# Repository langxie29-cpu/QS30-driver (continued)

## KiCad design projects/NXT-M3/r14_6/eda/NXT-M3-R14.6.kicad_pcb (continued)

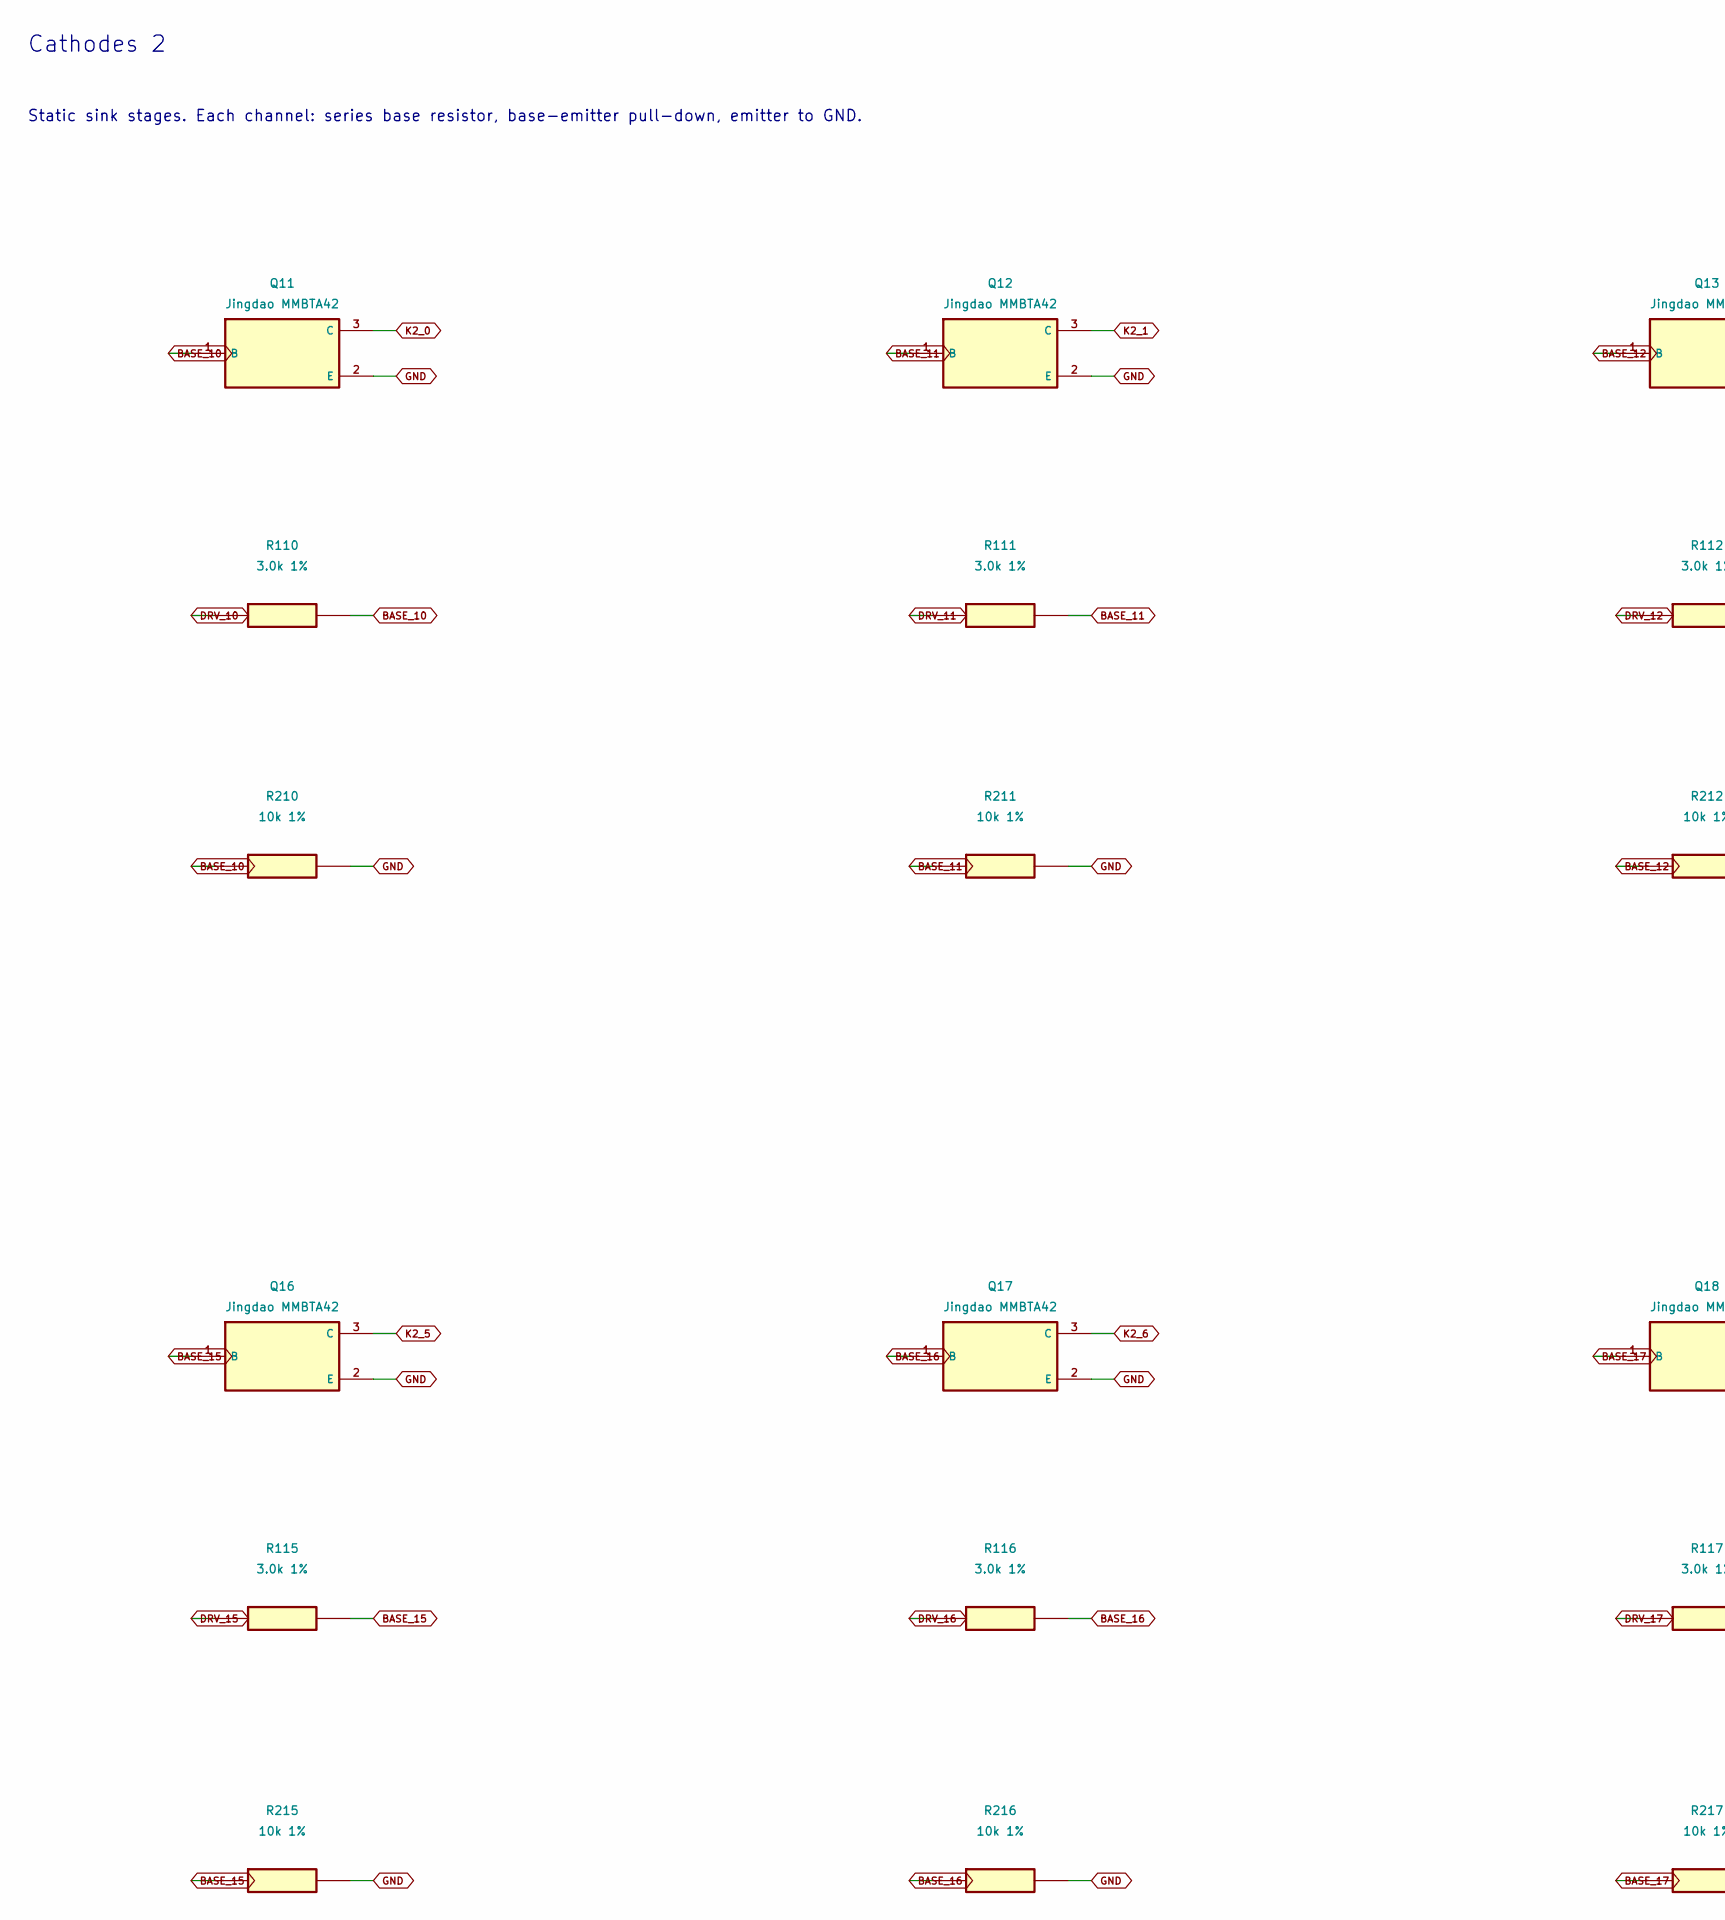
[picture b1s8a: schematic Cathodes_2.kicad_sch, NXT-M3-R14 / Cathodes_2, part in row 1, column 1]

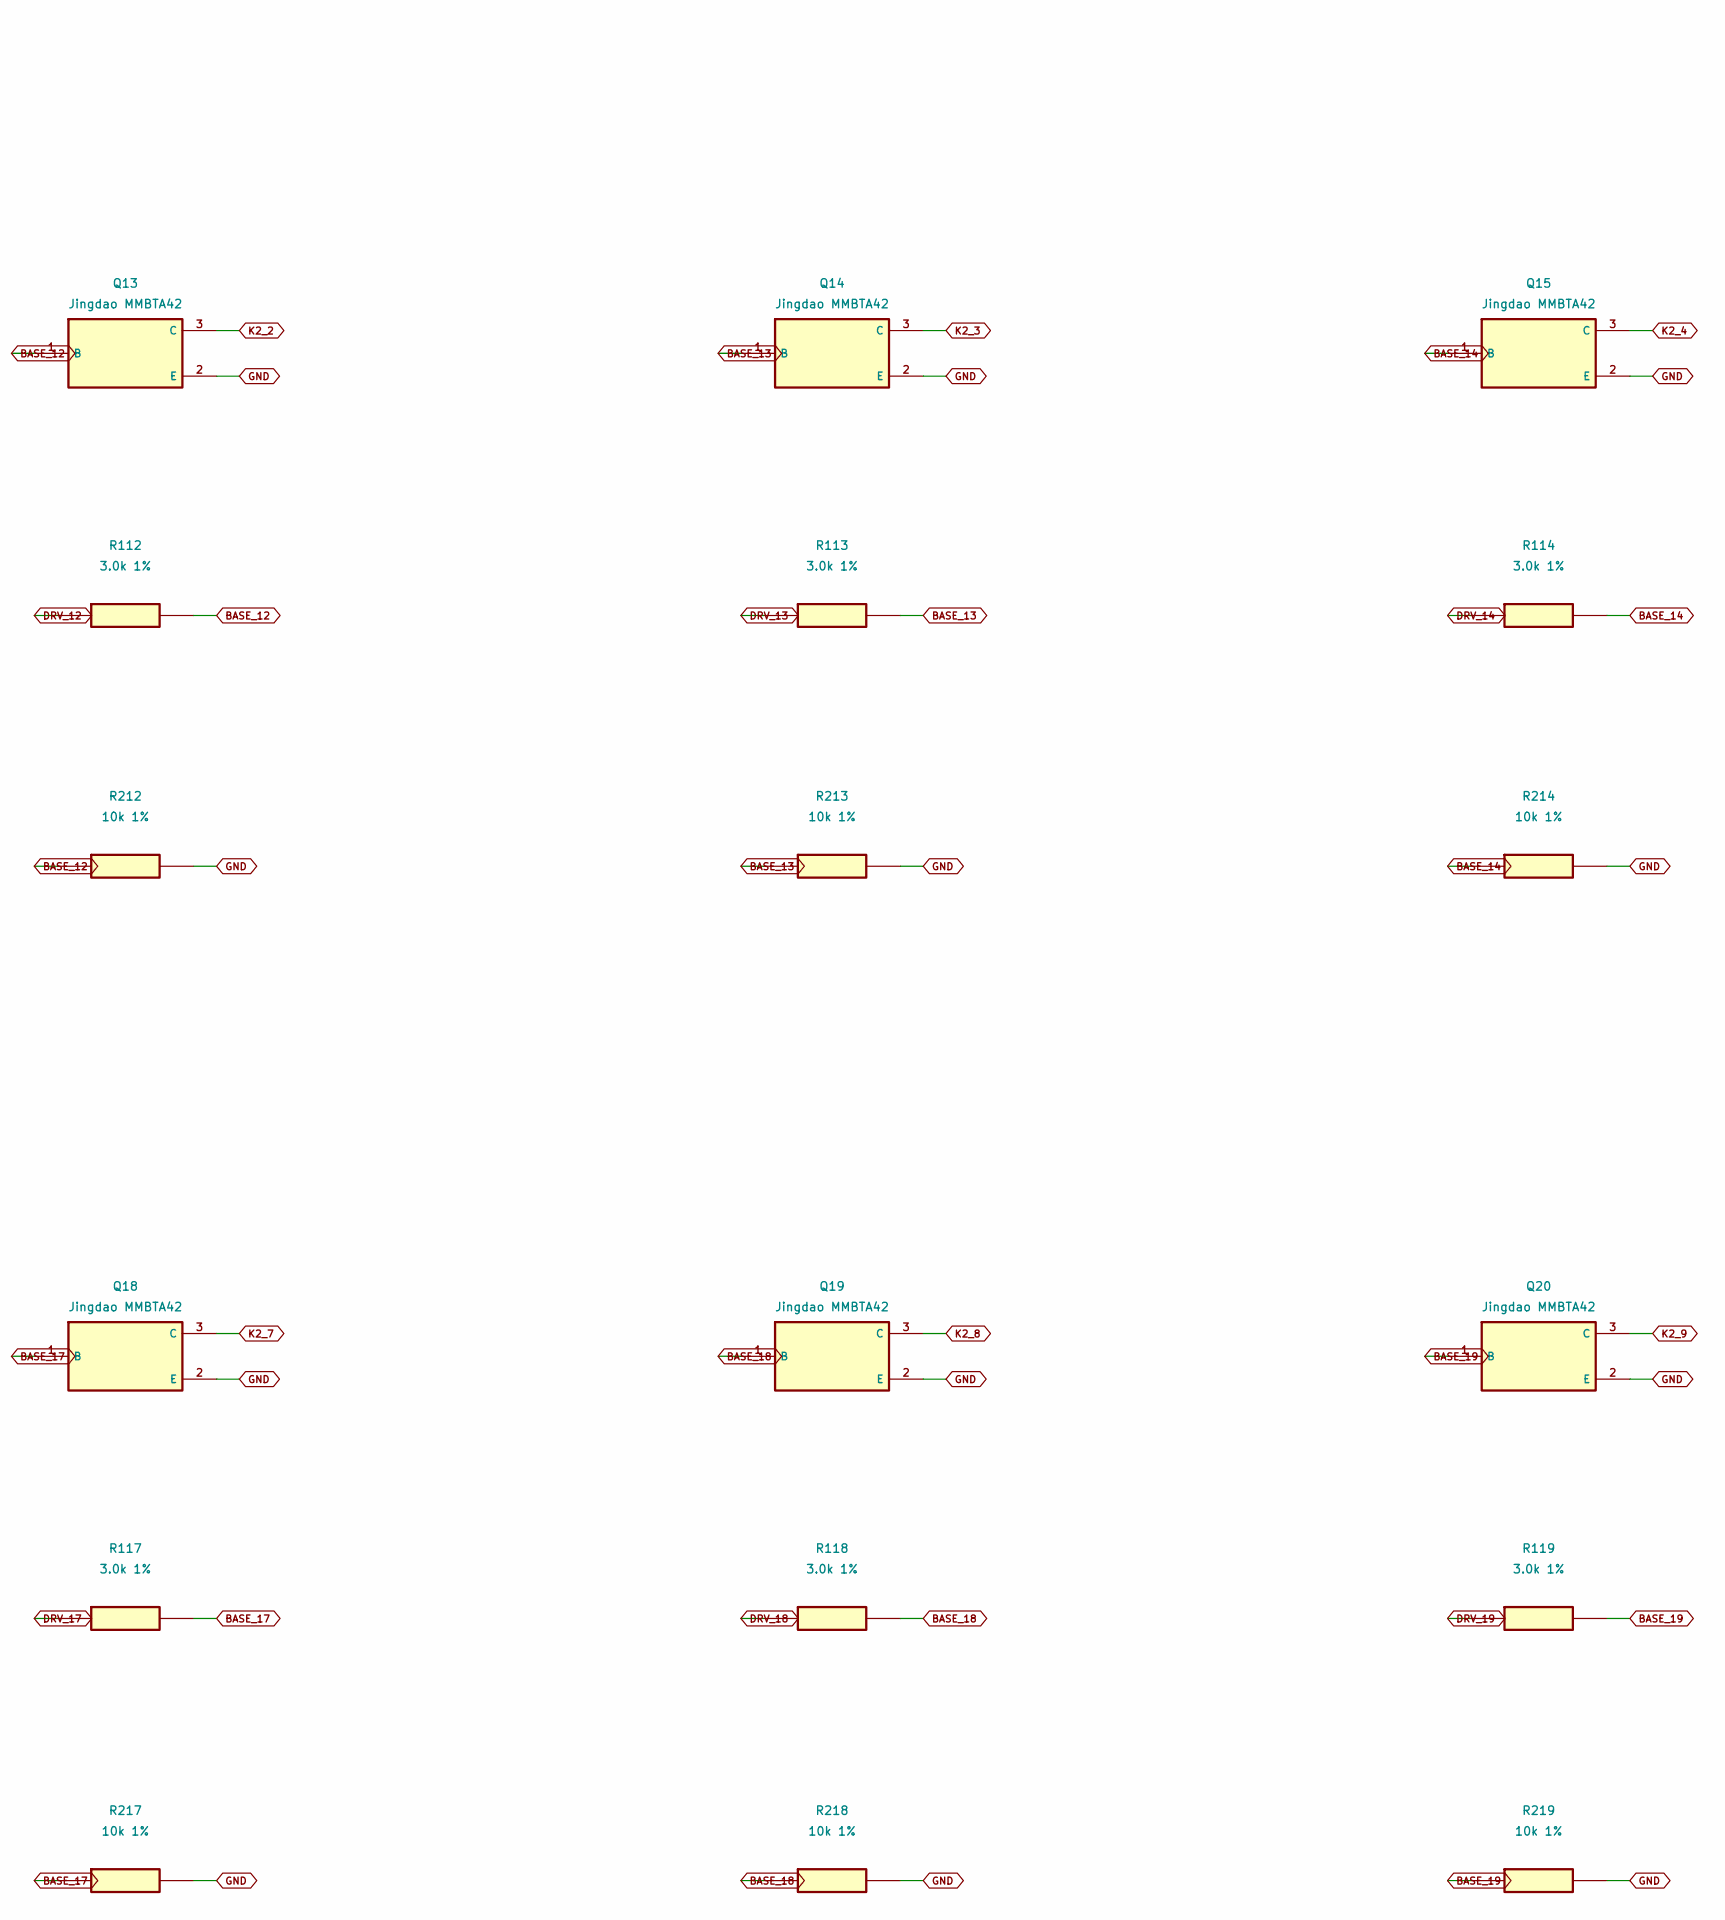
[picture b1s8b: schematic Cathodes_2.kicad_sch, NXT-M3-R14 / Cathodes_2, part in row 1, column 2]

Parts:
Q11, Q12, Q13, Q14, Q15, Q16, Q17, Q18, Q19, Q20: Jingdao MMBTA42; Jingdao_MMBTA42_nominal; MPN MMBTA42 / C4749118
R110, R111, R112, R113, R114, R115, R116, R117, R118, R119: 3.0k 1%; R_0603_1608Metric; MPN RC0603FR-073KL
R210, R211, R212, R213, R214, R215, R216, R217, R218, R219: 10k 1%; R_0603_1608Metric; MPN RC0603FR-0710KL

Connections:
BASE_10: Q11.1 (B), R110.2, R210.1
BASE_11: Q12.1 (B), R111.2, R211.1
BASE_12: Q13.1 (B), R112.2, R212.1
BASE_13: Q14.1 (B), R113.2, R213.1
BASE_14: Q15.1 (B), R114.2, R214.1
BASE_15: Q16.1 (B), R115.2, R215.1
BASE_16: Q17.1 (B), R116.2, R216.1
BASE_17: Q18.1 (B), R117.2, R217.1
BASE_18: Q19.1 (B), R118.2, R218.1
BASE_19: Q20.1 (B), R119.2, R219.1
DRV_10: R110.1; also elsewhere on the board
DRV_11: R111.1; also elsewhere on the board
DRV_12: R112.1; also elsewhere on the board
DRV_13: R113.1; also elsewhere on the board
DRV_14: R114.1; also elsewhere on the board
DRV_15: R115.1; also elsewhere on the board
DRV_16: R116.1; also elsewhere on the board
DRV_17: R117.1; also elsewhere on the board
DRV_18: R118.1; also elsewhere on the board
DRV_19: R119.1; also elsewhere on the board
GND: Q11.2 (E), Q12.2 (E), Q13.2 (E), Q14.2 (E), Q15.2 (E), Q16.2 (E), Q17.2 (E), Q18.2 (E), Q19.2 (E), Q20.2 (E), R210.2, R211.2, R212.2, R213.2, R214.2, R215.2, R216.2, R217.2, R218.2, R219.2; also elsewhere on the board
K2_0: Q11.3 (C); also elsewhere on the board
K2_1: Q12.3 (C); also elsewhere on the board
K2_2: Q13.3 (C); also elsewhere on the board
K2_3: Q14.3 (C); also elsewhere on the board
K2_4: Q15.3 (C); also elsewhere on the board
K2_5: Q16.3 (C); also elsewhere on the board
K2_6: Q17.3 (C); also elsewhere on the board
K2_7: Q18.3 (C); also elsewhere on the board
K2_8: Q19.3 (C); also elsewhere on the board
K2_9: Q20.3 (C); also elsewhere on the board

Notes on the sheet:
Cathodes 2
Static sink stages. Each channel: series base resistor, base-emitter pull-down, emitter to GND.

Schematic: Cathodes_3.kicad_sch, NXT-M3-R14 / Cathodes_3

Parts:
Q21, Q22, Q23, Q24, Q25, Q26, Q27, Q28, Q29, Q30: Jingdao MMBTA42; Jingdao_MMBTA42_nominal; MPN MMBTA42 / C4749118
R120, R121, R122, R123, R124, R125, R126, R127, R128, R129: 3.0k 1%; R_0603_1608Metric; MPN RC0603FR-073KL
R220, R221, R222, R223, R224, R225, R226, R227, R228, R229: 10k 1%; R_0603_1608Metric; MPN RC0603FR-0710KL

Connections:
BASE_20: Q21.1 (B), R120.2, R220.1
BASE_21: Q22.1 (B), R121.2, R221.1
BASE_22: Q23.1 (B), R122.2, R222.1
BASE_23: Q24.1 (B), R123.2, R223.1
BASE_24: Q25.1 (B), R124.2, R224.1
BASE_25: Q26.1 (B), R125.2, R225.1
BASE_26: Q27.1 (B), R126.2, R226.1
BASE_27: Q28.1 (B), R127.2, R227.1
BASE_28: Q29.1 (B), R128.2, R228.1
BASE_29: Q30.1 (B), R129.2, R229.1
DRV_20: R120.1; also elsewhere on the board
DRV_21: R121.1; also elsewhere on the board
DRV_22: R122.1; also elsewhere on the board
DRV_23: R123.1; also elsewhere on the board
DRV_24: R124.1; also elsewhere on the board
DRV_25: R125.1; also elsewhere on the board
DRV_26: R126.1; also elsewhere on the board
DRV_27: R127.1; also elsewhere on the board
DRV_28: R128.1; also elsewhere on the board
DRV_29: R129.1; also elsewhere on the board
GND: Q21.2 (E), Q22.2 (E), Q23.2 (E), Q24.2 (E), Q25.2 (E), Q26.2 (E), Q27.2 (E), Q28.2 (E), Q29.2 (E), Q30.2 (E), R220.2, R221.2, R222.2, R223.2, R224.2, R225.2, R226.2, R227.2, R228.2, R229.2; also elsewhere on the board
K3_0: Q21.3 (C); also elsewhere on the board
K3_1: Q22.3 (C); also elsewhere on the board
K3_2: Q23.3 (C); also elsewhere on the board
K3_3: Q24.3 (C); also elsewhere on the board
K3_4: Q25.3 (C); also elsewhere on the board
K3_5: Q26.3 (C); also elsewhere on the board
K3_6: Q27.3 (C); also elsewhere on the board
K3_7: Q28.3 (C); also elsewhere on the board
K3_8: Q29.3 (C); also elsewhere on the board
K3_9: Q30.3 (C); also elsewhere on the board

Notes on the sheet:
Cathodes 3
Static sink stages. Each channel: series base resistor, base-emitter pull-down, emitter to GND.

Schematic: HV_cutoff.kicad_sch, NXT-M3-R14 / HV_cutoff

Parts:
C25: 4.7n; C_0603_1608Metric; not fitted
C26: 10n; C_0603_1608Metric; not fitted
C27: 100n 25V; C_0603_1608Metric; not fitted
C28: 22u 16V; C_1206_3216Metric; not fitted
R40: DNP power-link open; R_1206_3216Metric; not fitted
R41: 36.5k; R_0603_1608Metric; not fitted
R42, R44, R45: 10k; R_0603_1608Metric; not fitted
R43: 2.00k; R_0603_1608Metric; not fitted
U11: TPS259474LRPWR; TI_RPW0010A_IN_OUT_escape; MPN TPS259474LRPWR; not fitted

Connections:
5V_HV: C28.1, R45.1, U11.6 (OUT); also elsewhere on the board
5V_PROT: R40.1; also elsewhere on the board
ARMED: U11.1 (EN); also elsewhere on the board
CUT_DVDT: C25.1, U11.7 (DVDT)
CUT_ILM: R43.1, U11.9 (ILM)
CUT_OVLO: R41.2, R42.1, U11.2 (OVLO)
CUT_PGTH: R44.1, U11.4 (PGTH)
CUT_TIMER: C26.1, U11.10 (ITIMER)
GND: C25.2, C26.2, C27.2, C28.2, R42.2, R43.2, R44.2, R45.2, U11.8 (GND); also elsewhere on the board
HV_ISOLATE_IN: C27.1, R40.2, R41.1, U11.5 (IN)

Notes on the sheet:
HV cutoff
R40 open DNP. eFuse branch and converter DNP for engineering HOLD. Components downstream of R40 can still store energy.
HV STOP deasserts ARMED through U8 hardware clear. R40 remains physically open DNP.

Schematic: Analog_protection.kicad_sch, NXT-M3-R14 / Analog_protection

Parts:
C29, C30, C32, C33, C34: 100n; C_0603_1608Metric
C31, C35, C36: 100p; C_0603_1608Metric
R46, R48, R51, R53: 10k; R_0603_1608Metric
R47: 93.1k; R_0603_1608Metric
R49: 470R; R_0603_1608Metric
R50: 64.9k; R_0603_1608Metric
R52: 47k; R_0603_1608Metric
R60, R61, R62, R63: 499k 1% HV; R_2512_6332Metric; not fitted
R64: 13.3k 1%; R_0603_1608Metric
R65, R66, R67, R68: 453k 1% HV; R_2512_6332Metric; not fitted
R69: 42.2k 1%; R_0603_1608Metric
U12: REF3312AIDBZR; SOT-23; MPN REF3312AIDBZR
U13, U14: TLV1702DGKR; TI_DGK0008A_VSSOP8; MPN TLV1702DGKR
U15: SN74LVC1G08DBVR; SOT-23-5; MPN SN74LVC1G08DBVR

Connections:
3V3: C29.1, C32.1, C33.1, C34.1, R46.1, R53.1, U12.1 (IN), U13.8 (VCC), U14.8 (VCC), U15.5 (VCC); also elsewhere on the board
ARMED: U15.1 (A); also elsewhere on the board
BIAS_OK: R46.2, U14.7 (OUT2), U15.2 (B)
BIAS_S: R50.2, R51.1, U14.5 (P2)
CS_FILT: C31.1, R49.2, U13.6 (N2)
FAULT_N: U13.1 (OUT1), U13.7 (OUT2); also elsewhere on the board
GATE_BIAS: R50.1; also elsewhere on the board
GND: C29.2, C30.2, C31.2, C32.2, C33.2, C34.2, C35.2, C36.2, R48.2, R51.2, R52.2, R64.2, R69.2, U12.3 (GND), U13.4 (GND), U14.4 (GND), U15.3 (GND); also elsewhere on the board
HV_BUS: R60.1, R65.1; also elsewhere on the board
HV_ISENSE: R49.1; also elsewhere on the board
HV_OVP_S: C35.1, R63.2, R64.1, U13.2 (N1)
HV_OVP_S_1: R60.2, R61.1
HV_OVP_S_2: R61.2, R62.1
HV_OVP_S_3: R62.2, R63.1
HV_READY: R53.2; also elsewhere on the board
HV_RES_S: C36.1, R68.2, R69.1, U14.2 (N1)
HV_RES_S_1: R65.2, R66.1
HV_RES_S_2: R66.2, R67.1
HV_RES_S_3: R67.2, R68.1
OCP_REF: R47.2, R48.1, U13.5 (P2)
PWM_PERMIT: R52.1, U15.4 (Y); also elsewhere on the board
REF_1V25: C30.1, R47.1, U12.2 (OUT), U13.3 (P1), U14.3 (P1), U14.6 (N2)
RESIDUAL_OK: U14.1 (OUT1); also elsewhere on the board

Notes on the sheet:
Analog protection
Separate divider inputs for OVP and residual voltage. Detection coverage, hysteresis, delay and diagnostics remain open.

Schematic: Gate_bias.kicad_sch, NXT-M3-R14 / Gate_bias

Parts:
C37: 4.7u 16V; C_0805_2012Metric; not fitted
C38: 4.7u 25V; C_1206_3216Metric; not fitted
C39: 100n; C_0603_1608Metric; not fitted
D2: SS14; D_SMA; MPN SS14; not fitted
L2: 10uH; L_Bourns-SRN4018; MPN SRN4018-100M; not fitted
R70: 845k; R_0603_1608Metric; not fitted
R71: 100k; R_0603_1608Metric; not fitted
U16: TPS61040DBVR; SOT-23-5; MPN TPS61040DBVR; not fitted

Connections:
5V_HV: C37.1, L2.1, U16.4 (EN), U16.5 (VIN); also elsewhere on the board
BIAS_FB: R70.2, R71.1, U16.3 (FB)
BIAS_SW: D2.2 (A), L2.2, U16.1 (SW)
GATE_BIAS: C38.1, C39.1, D2.1 (K), R70.1; also elsewhere on the board
GND: C37.2, C38.2, C39.2, R71.2, U16.2 (GND); also elsewhere on the board

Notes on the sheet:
Gate bias
Provisional 11.6 V cell from the switched feed. Qualification includes disabled precharge, backfeed and sequencing.

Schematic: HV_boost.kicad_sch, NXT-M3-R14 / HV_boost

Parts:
C40: 2.2u 16V; C_0805_2012Metric; not fitted
C41: 100n; C_0603_1608Metric; not fitted
C42: 100p; C_0603_1608Metric; not fitted
C43: 10n COMP candidate; C_0603_1608Metric; not fitted
C44: 100p COMP candidate; C_0603_1608Metric; not fitted
C45: 1u 25V; C_0805_2012Metric; not fitted
C46: 100n 16V; C_0603_1608Metric; not fitted
C47: 3.3u 450V 10%; TDK_B32774M4335K000; MPN B32774M4335K000; not fitted
C48: 100p 1kV C0G snubber candidate; Kemet_C2220_HV_Density_B; MPN C2220C101JDGACTU; not fitted
D3: ES1G-13-F; D_SMA; MPN ES1G-13-F; not fitted
L3: 22uH; L_Coilcraft_MSS1278-XXX; MPN MSS1278-223MLD; not fitted
Q32: STD13N60M2; TO-252-2; MPN STD13N60M2; not fitted
R72: 100R; R_0603_1608Metric; not fitted
R73: 50mR Kelvin candidate; R_2512_6332Metric; MPN WSL2512R0500FEA; not fitted
R74: 10R; R_0603_1608Metric; not fitted
R75: 4.7R; R_0603_1608Metric; not fitted
R76, R77: 10k; R_0603_1608Metric; not fitted
R78: 47k; R_0603_1608Metric; not fitted
R79: 220k RT candidate; R_0603_1608Metric; not fitted
R80: 10k COMP candidate; R_0603_1608Metric; not fitted
R81, R82, R83, R84: 422k 0.1% HV; R_2512_6332Metric; not fitted
R85: 10k 0.1%; R_0603_1608Metric; not fitted
R86: 100R snubber TBD; R_2512_6332Metric; not fitted
U17: LM5155DSSR; WSON-12-1EP_3x2mm_P0.5mm_EP1x2.65; MPN LM5155DSSR; not fitted
U18: UCC27511DBVR; SOT-23-6; MPN UCC27511DBVR; not fitted

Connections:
5V_HV: C46.1, L3.1, U17.1 (BIAS); also elsewhere on the board
COMP_Z: C43.1, R80.2
GATE_BIAS: C45.1, U18.1 (VDD); also elsewhere on the board
GATE_HV: Q32.1 (G), R74.2, R75.2, R76.1
GATE_SNK: R75.1, U18.3 (OUTL)
GATE_SRC: R74.1, U18.2 (OUTH)
GND: C40.2, C41.2, C42.2, C43.2, C44.2, C45.2, C46.2, C47.2, C48.2, R73.2, R78.2, R79.2, R85.2, U17.4 (PGND), U17.7 (AGND), U17.13 (EP), U18.4 (GND), U18.5 (IN_MINUS); also elsewhere on the board
HV_BUS: C47.1, D3.1 (K), R81.1; also elsewhere on the board
HV_COMP: C44.1, R80.1, U17.6 (COMP)
HV_CS: C42.1, R72.2, U17.5 (CS)
HV_FB: R84.2, R85.1, U17.8 (FB)
HV_FB_1: R81.2, R82.1
HV_FB_2: R82.2, R83.1
HV_FB_3: R83.2, R84.1
HV_ISENSE: Q32.3 (S), R72.1, R73.1, R76.2; also elsewhere on the board
HV_READY: U17.11 (PGOOD); also elsewhere on the board
HV_RT: R79.1, U17.10 (RT)
HV_SS: C41.1, U17.9 (SS)
HV_UVLO: R77.2, R78.1, U17.12 (UVLO)
HV_VCC: C40.1, U17.2 (VCC)
PWM_PERMIT: R77.1; also elsewhere on the board
PWM_RAW: U17.3 (GATE), U18.6 (IN_PLUS)
SNUB: C48.1, R86.2
SW_HV: D3.2 (A), L3.2, Q32.2 (D), R86.1

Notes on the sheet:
HV boost
DCM boost design candidate. Bias, RT, slope/current limit, loop compensation, peak stress and snubber are unqualified.

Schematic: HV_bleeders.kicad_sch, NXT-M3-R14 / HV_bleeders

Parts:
R400, R401, R402, R403, R404, R405, R406, R407: 124k 1% HV; R_2512_6332Metric

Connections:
BLEED_1_1: R400.2, R401.1
BLEED_1_2: R401.2, R402.1
BLEED_1_3: R402.2, R403.1
BLEED_2_1: R404.2, R405.1
BLEED_2_2: R405.2, R406.1
BLEED_2_3: R406.2, R407.1
GND: R403.2, R407.2; also elsewhere on the board
HV_BUS: R400.1, R404.1; also elsewhere on the board

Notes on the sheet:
HV bleeders
Two independent passive paths. Each chain has four series resistors and must retain separate layout paths.

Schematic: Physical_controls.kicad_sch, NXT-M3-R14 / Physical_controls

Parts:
C60, C61, C62, C63: 10n; C_0603_1608Metric
C64: 1n; C_0603_1608Metric
D10, D11, D12, D13, D15: TPD1E10B06; D_SOD-523; MPN TPD1E10B06DYAR
D14: BAT54H; D_SOD-123F; MPN BAT54H,115; not fitted
J5: J_BTN / dry contacts; JST_GH_BM06B-GHS-TBT_1x06-1MP_P1.25mm_Vertical; MPN BM06B-GHS-TBT(LF)(SN); not fitted
J6: HV STOP / NC dry loop; JST_PH_S2B-PH-K_1x02_P2.00mm_Horizontal; MPN S2B-PH-K-S(LF)(SN)
Q35: 2N7002BK / STOP sink; SOT-23; MPN 2N7002BK,215
R500, R501, R502, R503: 1k 1%; R_0603_1608Metric
R504, R505, R506, R507: 10k 1%; R_0603_1608Metric
R508: 330R 1%; R_0603_1608Metric; not fitted
R509: 220R 1%; R_0603_1608Metric
R510: 3.3k 1%; R_0603_1608Metric

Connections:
3V3: R504.1, R505.1, R506.1, R507.1, R508.1, R510.1; also elsewhere on the board
3V3_AUX: D14.1 (K), J5.6 (3V3_AUX)
AUX1: D12.1 (IO), J5.4 (AUX1), R502.1
AUX1_GPIO: C62.1, R502.2, R506.2; also elsewhere on the board
AUX2: D13.1 (IO), J5.5 (AUX2), R503.1
AUX2_GPIO: C63.1, R503.2, R507.2; also elsewhere on the board
AUX_FEED: D14.2 (A), R508.2
BTN1: D10.1 (IO), J5.2 (BTN1), R500.1
BTN1_GPIO: C60.1, R500.2, R504.2; also elsewhere on the board
BTN2: D11.1 (IO), J5.3 (BTN2), R501.1
BTN2_GPIO: C61.1, R501.2, R505.2; also elsewhere on the board
FAULT_N: Q35.3 (D); also elsewhere on the board
GND: C60.2, C61.2, C62.2, C63.2, C64.2, D10.2 (GND), D11.2 (GND), D12.2 (GND), D13.2 (GND), D15.2 (GND), J5.1 (GND), J5.MP, J6.2 (RETURN), Q35.2 (S); also elsewhere on the board
STOP_GATE: C64.1, Q35.1 (G), R509.2, R510.2
STOP_LOOP: D15.1 (IO), J6.1 (LOOP), R509.1

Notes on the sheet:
FUNCTION BUTTONS / ACCESSORY
J5 dry contacts to GND. Fit neither R508 nor D14 for the passive harness.
HARDWARE HV STOP
J6 external NC dry loop. Opening pulls FAULT_N low. Re-arm locally at J4.

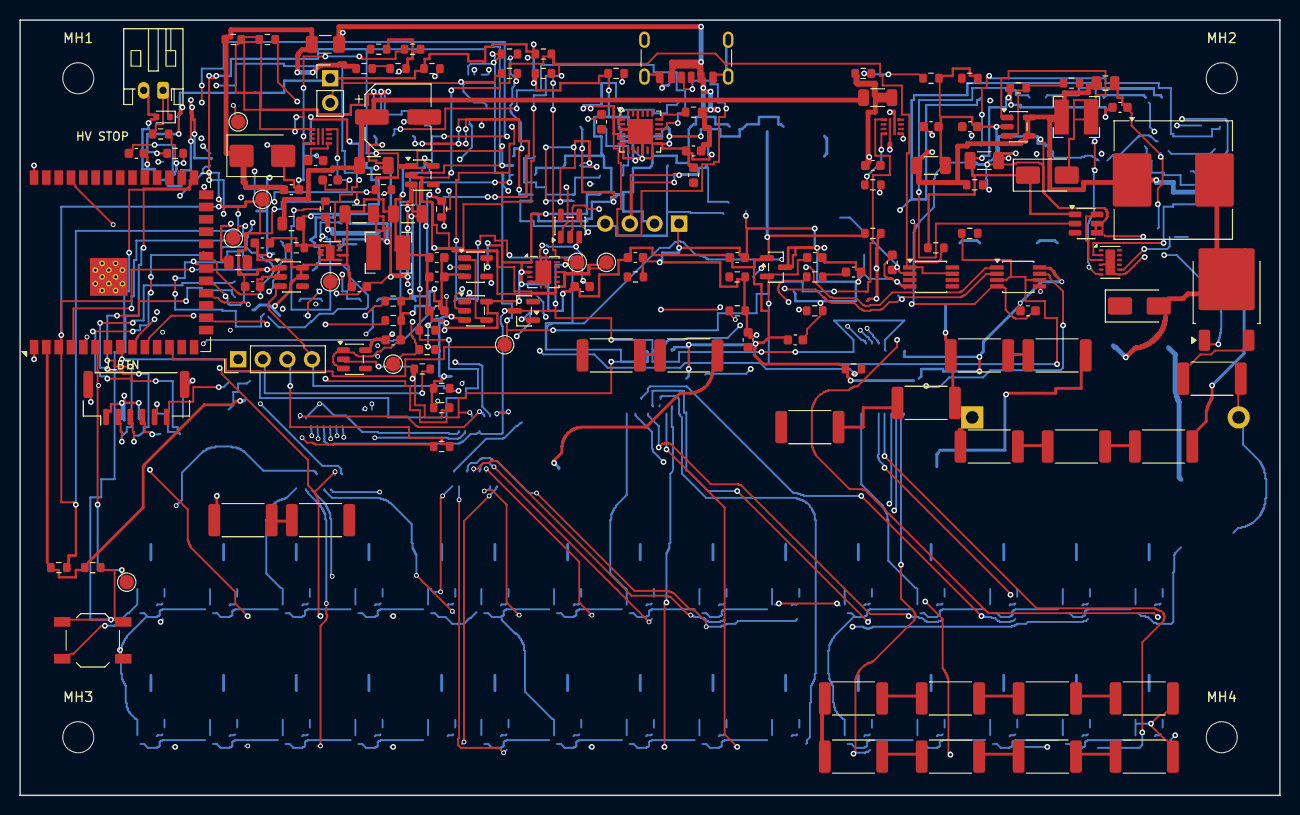
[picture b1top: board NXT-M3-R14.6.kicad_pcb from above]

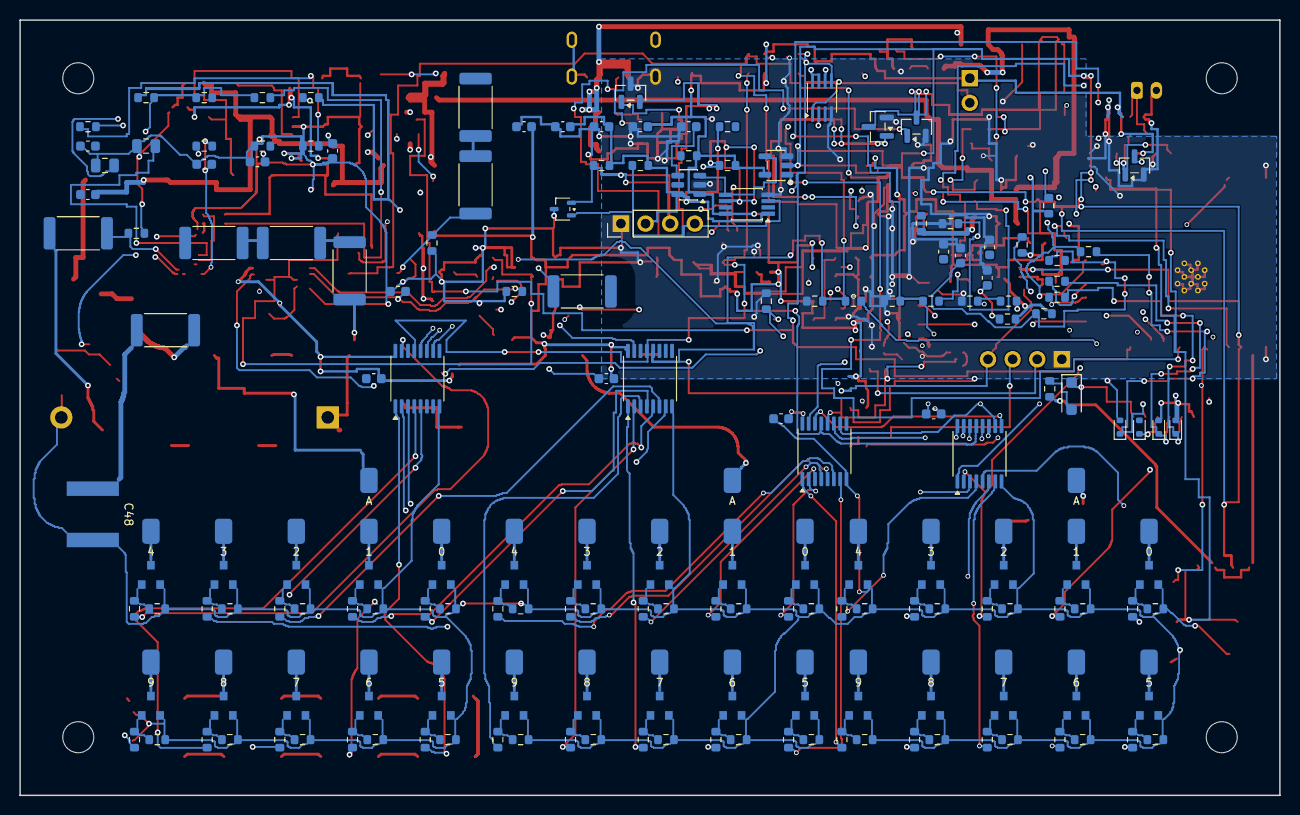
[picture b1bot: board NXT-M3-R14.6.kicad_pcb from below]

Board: 4 copper layers, 130.0 x 80.0 mm, 326 parts (177 on the bottom side), 218 nets.

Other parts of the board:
MH1, MH2, MH3, MH4: MountingHole_3.2mm_M3
R302, R303, R304, R305, R306, R307: 10k 1% HV 1W; R_2512_6332Metric
V1, V2, V3: QS30-1 / GZC13-F external hand-wire; Remote_Tube_11_SMD

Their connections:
ALIM_1: R302.2, R303.1
ALIM_2: R304.2, R305.1
ALIM_3: R306.2, R307.1
ANODE_1: R303.2, V1.1
ANODE_2: R305.2, V2.1
ANODE_3: R307.2, V3.1
HV_BUS: R302.1, R304.1, R306.1; also elsewhere on the board
K1_0: V1.3; also elsewhere on the board
K1_1: V1.13; also elsewhere on the board
K1_2: V1.12; also elsewhere on the board
K1_3: V1.11; also elsewhere on the board
K1_4: V1.10; also elsewhere on the board
K1_5: V1.9; also elsewhere on the board
K1_6: V1.7; also elsewhere on the board
K1_7: V1.6; also elsewhere on the board
K1_8: V1.5; also elsewhere on the board
K1_9: V1.4; also elsewhere on the board
K2_0: V2.3; also elsewhere on the board
K2_1: V2.13; also elsewhere on the board
K2_2: V2.12; also elsewhere on the board
K2_3: V2.11; also elsewhere on the board
K2_4: V2.10; also elsewhere on the board
K2_5: V2.9; also elsewhere on the board
K2_6: V2.7; also elsewhere on the board
K2_7: V2.6; also elsewhere on the board
K2_8: V2.5; also elsewhere on the board
K2_9: V2.4; also elsewhere on the board
K3_0: V3.3; also elsewhere on the board
K3_1: V3.13; also elsewhere on the board
K3_2: V3.12; also elsewhere on the board
K3_3: V3.11; also elsewhere on the board
K3_4: V3.10; also elsewhere on the board
K3_5: V3.9; also elsewhere on the board
K3_6: V3.7; also elsewhere on the board
K3_7: V3.6; also elsewhere on the board
K3_8: V3.5; also elsewhere on the board
K3_9: V3.4; also elsewhere on the board

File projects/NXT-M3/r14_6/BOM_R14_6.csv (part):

Reference,Value,MPN,Manufacturer,Footprint,Quantity,DNP,Supplier,Supplier_PN,MOQ,Price_Tier,Unit_Price_CNY,Purchase_Qty,Extended_Cost_CNY,Evidence_URL,Quote_Date,Alternate,Verification_Status
C1,100n 25V,,,Capacitor_SMD:C_0603_1608Metric,1,NO,,,,,,,,,,,MPN_TBD
C2,4.7n,,,Capacitor_SMD:C_0603_1608Metric,1,NO,,,,,,,,,,,MPN_TBD
C3,10n,,,Capacitor_SMD:C_0603_1608Metric,1,NO,,,,,,,,,,,MPN_TBD
C4,22u 16V,,,Capacitor_SMD:C_1206_3216Metric,1,NO,,,,,,,,,,,MPN_TBD
C5,100u 10V,,,Capacitor_SMD:CP_Elec_6.3x5.8,1,NO,,,,,,,,,,,MPN_TBD
C6,10u 16V,,,Capacitor_SMD:C_0805_2012Metric,1,NO,,,,,,,,,,,MPN_TBD
C7,22u 10V,,,Capacitor_SMD:C_1206_3216Metric,1,NO,,,,,,,,,,,MPN_TBD
C8,22u 10V,,,Capacitor_SMD:C_1206_3216Metric,1,NO,,,,,,,,,,,MPN_TBD
C9,100n,,,Capacitor_SMD:C_0603_1608Metric,1,NO,,,,,,,,,,,MPN_TBD
C10,10u 10V,,,Capacitor_SMD:C_0805_2012Metric,1,NO,,,,,,,,,,,MPN_TBD
C11,1u,,,Capacitor_SMD:C_0603_1608Metric,1,NO,,,,,,,,,,,MPN_TBD
C12,100n,,,Capacitor_SMD:C_0603_1608Metric,1,NO,,,,,,,,,,,MPN_TBD
C13,1n,,,Capacitor_SMD:C_0603_1608Metric,1,NO,,,,,,,,,,,MPN_TBD
C14,100n,,,Capacitor_SMD:C_0603_1608Metric,1,NO,,,,,,,,,,,MPN_TBD
C15,1u,,,Capacitor_SMD:C_0603_1608Metric,1,NO,,,,,,,,,,,MPN_TBD
C16,100n,,,Capacitor_SMD:C_0603_1608Metric,1,NO,,,,,,,,,,,MPN_TBD
C17,100n,,,Capacitor_SMD:C_0603_1608Metric,1,NO,,,,,,,,,,,MPN_TBD
C18,100n,,,Capacitor_SMD:C_0603_1608Metric,1,NO,,,,,,,,,,,MPN_TBD
C19,100n,,,Capacitor_SMD:C_0603_1608Metric,1,NO,,,,,,,,,,,MPN_TBD
C20,100n,,,Capacitor_SMD:C_0603_1608Metric,1,NO,,,,,,,,,,,MPN_TBD
C21,100n,,,Capacitor_SMD:C_0603_1608Metric,1,NO,,,,,,,,,,,MPN_TBD
C22,100n,,,Capacitor_SMD:C_0603_1608Metric,1,NO,,,,,,,,,,,MPN_TBD
C23,100n,,,Capacitor_SMD:C_0603_1608Metric,1,NO,,,,,,,,,,,MPN_TBD
C24,100n,,,Capacitor_SMD:C_0603_1608Metric,1,NO,,,,,,,,,,,MPN_TBD
C25,4.7n,,,Capacitor_SMD:C_0603_1608Metric,1,YES,,,,,,0,0,,,,MPN_TBD
C26,10n,,,Capacitor_SMD:C_0603_1608Metric,1,YES,,,,,,0,0,,,,MPN_TBD
C27,100n 25V,,,Capacitor_SMD:C_0603_1608Metric,1,YES,,,,,,0,0,,,,MPN_TBD
C28,22u 16V,,,Capacitor_SMD:C_1206_3216Metric,1,YES,,,,,,0,0,,,,MPN_TBD
C29,100n,,,Capacitor_SMD:C_0603_1608Metric,1,NO,,,,,,,,,,,MPN_TBD
C30,100n,,,Capacitor_SMD:C_0603_1608Metric,1,NO,,,,,,,,,,,MPN_TBD
C31,100p,,,Capacitor_SMD:C_0603_1608Metric,1,NO,,,,,,,,,,,MPN_TBD
C32,100n,,,Capacitor_SMD:C_0603_1608Metric,1,NO,,,,,,,,,,,MPN_TBD
C33,100n,,,Capacitor_SMD:C_0603_1608Metric,1,NO,,,,,,,,,,,MPN_TBD
C34,100n,,,Capacitor_SMD:C_0603_1608Metric,1,NO,,,,,,,,,,,MPN_TBD
C35,100p,,,Capacitor_SMD:C_0603_1608Metric,1,NO,,,,,,,,,,,MPN_TBD
C36,100p,,,Capacitor_SMD:C_0603_1608Metric,1,NO,,,,,,,,,,,MPN_TBD
C37,4.7u 16V,,,Capacitor_SMD:C_0805_2012Metric,1,YES,,,,,,0,0,,,,MPN_TBD
C38,4.7u 25V,,,Capacitor_SMD:C_1206_3216Metric,1,YES,,,,,,0,0,,,,MPN_TBD
C39,100n,,,Capacitor_SMD:C_0603_1608Metric,1,YES,,,,,,0,0,,,,MPN_TBD
C40,2.2u 16V,,,Capacitor_SMD:C_0805_2012Metric,1,YES,,,,,,0,0,,,,MPN_TBD
C41,100n,,,Capacitor_SMD:C_0603_1608Metric,1,YES,,,,,,0,0,,,,MPN_TBD
C42,100p,,,Capacitor_SMD:C_0603_1608Metric,1,YES,,,,,,0,0,,,,MPN_TBD
C43,10n COMP candidate,,,Capacitor_SMD:C_0603_1608Metric,1,YES,,,,,,0,0,,,,MPN_TBD
C44,100p COMP candidate,,,Capacitor_SMD:C_0603_1608Metric,1,YES,,,,,,0,0,,,,MPN_TBD
C45,1u 25V,,,Capacitor_SMD:C_0805_2012Metric,1,YES,,,,,,0,0,,,,MPN_TBD
C46,100n 16V,,,Capacitor_SMD:C_0603_1608Metric,1,YES,,,,,,0,0,,,,MPN_TBD
C47,3.3u 450V 10%,B32774M4335K000,TDK,R10_R10:TDK_B32774M4335K000,1,YES,,,,,,0,0,,,,IDENTIFIED_UNQUOTED
C48,100p 1kV C0G snubber candidate,C2220C101JDGACTU,KEMET,R14_6:Kemet_C2220_HV_Density_B,1,YES,Farnell,3505448,,,,0,0,https://no.farnell.com/kemet/c2220c101jdgactu/cap-100pf-1kv-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,,,IDENTIFIED_UNQUOTED
C49,100n,,,Capacitor_SMD:C_0603_1608Metric,1,NO,,,,,,,,,,,MPN_TBD
C50,100n,,,Capacitor_SMD:C_0603_1608Metric,1,NO,,,,,,,,,,,MPN_TBD
C51,100n,,,Capacitor_SMD:C_0603_1608Metric,1,NO,,,,,,,,,,,MPN_TBD
C52,1u 16V,,,Capacitor_SMD:C_0603_1608Metric,1,NO,,,,,,,,,,,MPN_TBD
C53,1u 10V,,,Capacitor_SMD:C_0603_1608Metric,1,NO,,,,,,,,,,,MPN_TBD
C54,1u 10V,,,Capacitor_SMD:C_0603_1608Metric,1,NO,,,,,,,,,,,MPN_TBD
C60,10n,,,Capacitor_SMD:C_0603_1608Metric,1,NO,,,,,,,,,,,MPN_TBD
C61,10n,,,Capacitor_SMD:C_0603_1608Metric,1,NO,,,,,,,,,,,MPN_TBD
C62,10n,,,Capacitor_SMD:C_0603_1608Metric,1,NO,,,,,,,,,,,MPN_TBD
C63,10n,,,Capacitor_SMD:C_0603_1608Metric,1,NO,,,,,,,,,,,MPN_TBD
C64,1n,,,Capacitor_SMD:C_0603_1608Metric,1,NO,,,,,,,,,,,MPN_TBD
D1,TPD2E2U06DCKR,TPD2E2U06DCKR,Texas Instruments,Package_TO_SOT_SMD:SOT-323_SC-70,1,NO,,,,,,,,https://www.ti.com/lit/ds/symlink/tpd2e2u06.pdf,,,IDENTIFIED_UNQUOTED
D2,SS14,SS14,,Diode_SMD:D_SMA,1,YES,,,,,,0,0,,,,GENERIC_PART_MANUFACTURER_TBD
D3,ES1G-13-F,ES1G-13-F,Diodes Incorporated,Diode_SMD:D_SMA,1,YES,DigiKey CT,ES1G-FDICT-ND,1,1+,5.40,0,0,https://www.digikey.cn/zh/products/detail/diodes-incorporate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,2026-11-22,,PUBLIC_PAGE_SNAPSHOT_CNY
D4,SMBJ6.0CA bidirectional,SMBJ6.0CA,,Diode_SMD:D_SMB,1,NO,,,,,,,,,,,GENERIC_PART_MANUFACTURER_TBD
D5,ESDA25L,ESDA25L,STMicroelectronics,Package_TO_SOT_SMD:SOT-23,1,NO,,,,,,,,https://www.st.com/resource/en/datasheet/esdal.pdf,,,IDENTIFIED_UNQUOTED
D10,TPD1E10B06,TPD1E10B06DYAR,Texas Instruments,Diode_SMD:D_SOD-523,1,NO,,,,,,,,https://www.ti.com/lit/ds/symlink/tpd1e10b06.pdf,,,IDENTIFIED_UNQUOTED
D11,TPD1E10B06,TPD1E10B06DYAR,Texas Instruments,Diode_SMD:D_SOD-523,1,NO,,,,,,,,https://www.ti.com/lit/ds/symlink/tpd1e10b06.pdf,,,IDENTIFIED_UNQUOTED
D12,TPD1E10B06,TPD1E10B06DYAR,Texas Instruments,Diode_SMD:D_SOD-523,1,NO,,,,,,,,https://www.ti.com/lit/ds/symlink/tpd1e10b06.pdf,,,IDENTIFIED_UNQUOTED
D13,TPD1E10B06,TPD1E10B06DYAR,Texas Instruments,Diode_SMD:D_SOD-523,1,NO,,,,,,,,https://www.ti.com/lit/ds/symlink/tpd1e10b06.pdf,,,IDENTIFIED_UNQUOTED
D14,BAT54H,"BAT54H,115",Nexperia,Diode_SMD:D_SOD-123F,1,YES,,,,,,0,0,https://assets.nexperia.com/documents/data-sheet/BAT54H.pdf,,,IDENTIFIED_UNQUOTED
D15,TPD1E10B06,TPD1E10B06DYAR,Texas Instruments,Diode_SMD:D_SOD-523,1,NO,,,,,,,,https://www.ti.com/lit/ds/symlink/tpd1e10b06.pdf,,,IDENTIFIED_UNQUOTED
F1,2 A candidate,0467002.NR,Littelfuse,Fuse:Fuse_1206_3216Metric,1,NO,,,,,,,,,,,IDENTIFIED_UNQUOTED
J1,USB-C 5 V power only,USB4125-GF-A,GCT,Connector_USB:USB_C_Receptacle_GCT_USB4125-xx-x_6P_TopMnt_Horizontal,1,NO,,,,,,,,https://gct.co/files/drawings/usb4125.pdf,,,IDENTIFIED_UNQUOTED
J2,3V3 UART ROM service / no power,,,Connector_PinHeader_2.54mm:PinHeader_1x04_P2.54mm_Vertical,1,NO,,,,,,,,,,,MPN_TBD
J3,0.91 inch OLED harness TBD,,,Connector_PinHeader_2.54mm:PinHeader_1x04_P2.54mm_Vertical,1,NO,,,,,,,,,,,MPN_TBD
J4,Service ARM contacts momentary,,,Connector_PinHeader_2.54mm:PinHeader_1x02_P2.54mm_Vertical,1,NO,,,,,,,,,,,MPN_TBD
J5,J_BTN / dry contacts,BM06B-GHS-TBT(LF)(SN),JST,Connector_JST:JST_GH_BM06B-GHS-TBT_1x06-1MP_P1.25mm_Vertical,1,YES,,,,,,0,0,https://www.jst-mfg.com/product/pdf/eng/eGH.pdf,,,IDENTIFIED_UNQUOTED
J6,HV STOP / NC dry loop,S2B-PH-K-S(LF)(SN),JST,Connector_JST:JST_PH_S2B-PH-K_1x02_P2.00mm_Horizontal,1,NO,,,,,,,,https://www.jst-mfg.com/product/pdf/eng/ePH.pdf,,,IDENTIFIED_UNQUOTED
L1,2.2uH,SRN4018-2R2M,Bourns,Inductor_SMD:L_Bourns-SRN4018,1,NO,,,,,,,,,,,IDENTIFIED_UNQUOTED
L2,10uH,SRN4018-100M,Bourns,Inductor_SMD:L_Bourns-SRN4018,1,YES,,,,,,0,0,,,,IDENTIFIED_UNQUOTED
L3,22uH,MSS1278-223MLD,Coilcraft,Inductor_SMD:L_Coilcraft_MSS1278-XXX,1,YES,,,,,,0,0,,,,IDENTIFIED_UNQUOTED
Q1,Jingdao MMBTA42,MMBTA42,Shandong Jingdao Microelectronics,R14_4:Jingdao_MMBTA42_nominal,1,NO,LCSC,C4749118,,,,,,https://item.szlcsc.com/5321818.html,,,IDENTIFIED_UNQUOTED
Q2,Jingdao MMBTA42,MMBTA42,Shandong Jingdao Microelectronics,R14_4:Jingdao_MMBTA42_nominal,1,NO,LCSC,C4749118,,,,,,https://item.szlcsc.com/5321818.html,,,IDENTIFIED_UNQUOTED
Q3,Jingdao MMBTA42,MMBTA42,Shandong Jingdao Microelectronics,R14_4:Jingdao_MMBTA42_nominal,1,NO,LCSC,C4749118,,,,,,https://item.szlcsc.com/5321818.html,,,IDENTIFIED_UNQUOTED
Q4,Jingdao MMBTA42,MMBTA42,Shandong Jingdao Microelectronics,R14_4:Jingdao_MMBTA42_nominal,1,NO,LCSC,C4749118,,,,,,https://item.szlcsc.com/5321818.html,,,IDENTIFIED_UNQUOTED
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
